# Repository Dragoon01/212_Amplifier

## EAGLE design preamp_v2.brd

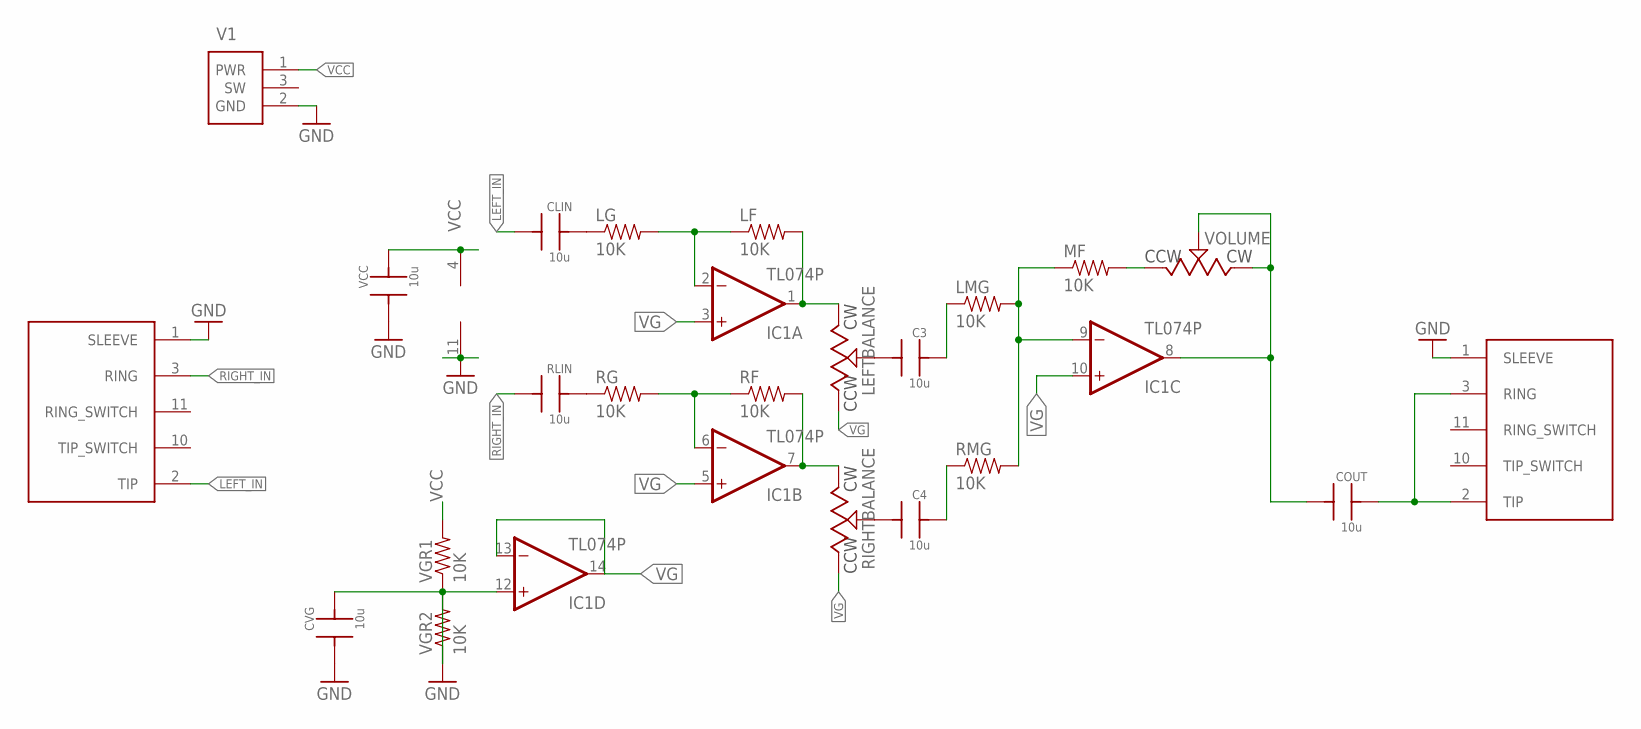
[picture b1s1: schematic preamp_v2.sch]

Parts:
C3, C4: 10u; C322
CLIN: 10u; C322
COUT: 10u; C322
CVG: 10u; C322
IC1: TL074P; DIL14
LEFTBALANCE: POTENTIOMETER3362P; 3362P
LF: 10K; AXIAL-0.4
LG: 10K; AXIAL-0.4
LMG: 10K; AXIAL-0.4
MF: 10K; AXIAL-0.4
RF: 10K; AXIAL-0.4
RG: 10K; AXIAL-0.4
RIGHTBALANCE: POTENTIOMETER3362P; 3362P
RLIN: 10u; C322
RMG: 10K; AXIAL-0.4
U$3, U$4: AUDIO_5_CONDUCTOR; SJ1-3525N
V1: POWER_JACK; PJ-102AH
VCC: 10u; C322
VGR1, VGR2: 10K; AXIAL-0.4
VOLUME: POTENTIOMETER3362P; 3362P

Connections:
GND: CVG.1, IC1.11 (V-), U$3.1 (SLEEVE), U$4.1 (SLEEVE), V1.2 (GND), VCC.1, VGR2.P$2 (2)
LEFT_IN: CLIN.1, U$3.2 (TIP)
unnamed: IC1.2 (-IN), LF.P$1 (1), LG.P$2 (2)
unnamed: IC1.6 (-IN), RF.P$1 (1), RG.P$2 (2)
unnamed: IC1.7 (OUT), RF.P$2 (2), RIGHTBALANCE.3 (CW)
unnamed: IC1.1 (OUT), LEFTBALANCE.3 (CW), LF.P$2 (2)
unnamed: RG.P$1 (1), RLIN.2
unnamed: CLIN.2, LG.P$1 (1)
unnamed: CVG.2, IC1.12 (+IN), VGR1.P$1 (1), VGR2.P$1 (1)
unnamed: C3.1, LEFTBALANCE.2 (WIPER)
unnamed: C3.2, LMG.P$1 (1)
unnamed: C4.2, RMG.P$1 (1)
unnamed: IC1.9 (-IN), LMG.P$2 (2), MF.P$1 (1), RMG.P$2 (2)
unnamed: C4.1, RIGHTBALANCE.2 (WIPER)
unnamed: COUT.1, IC1.8 (OUT), VOLUME.2 (WIPER), VOLUME.3 (CW)
unnamed: COUT.2, U$4.2 (TIP), U$4.3 (RING)
unnamed: MF.P$2 (2), VOLUME.1 (CCW)
RIGHT_IN: RLIN.1, U$3.3 (RING)
SW: V1.3 (SW)
VCC: IC1.4 (V+), V1.1 (PWR), VCC.2, VGR1.P$2 (2)
VG: IC1.3 (+IN), IC1.5 (+IN), IC1.10 (+IN), IC1.13 (-IN), IC1.14 (OUT), LEFTBALANCE.1 (CCW), RIGHTBALANCE.1 (CCW)

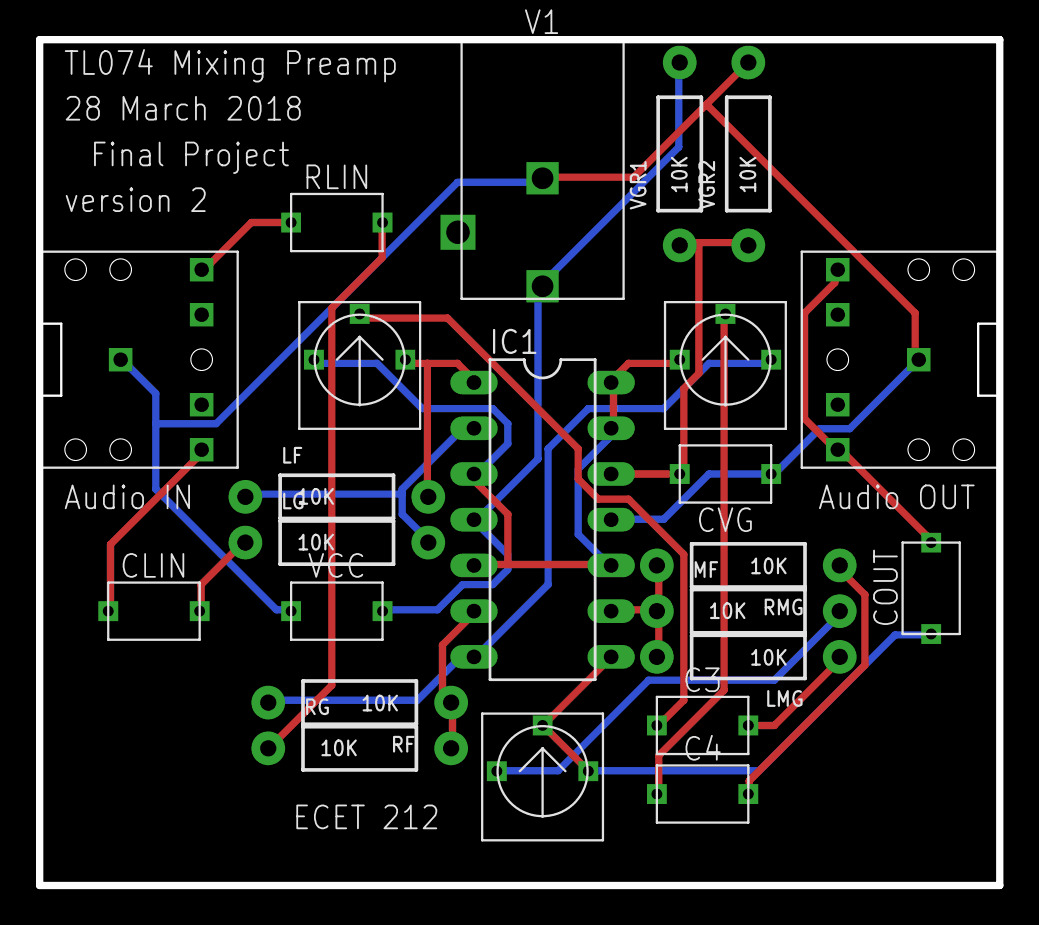
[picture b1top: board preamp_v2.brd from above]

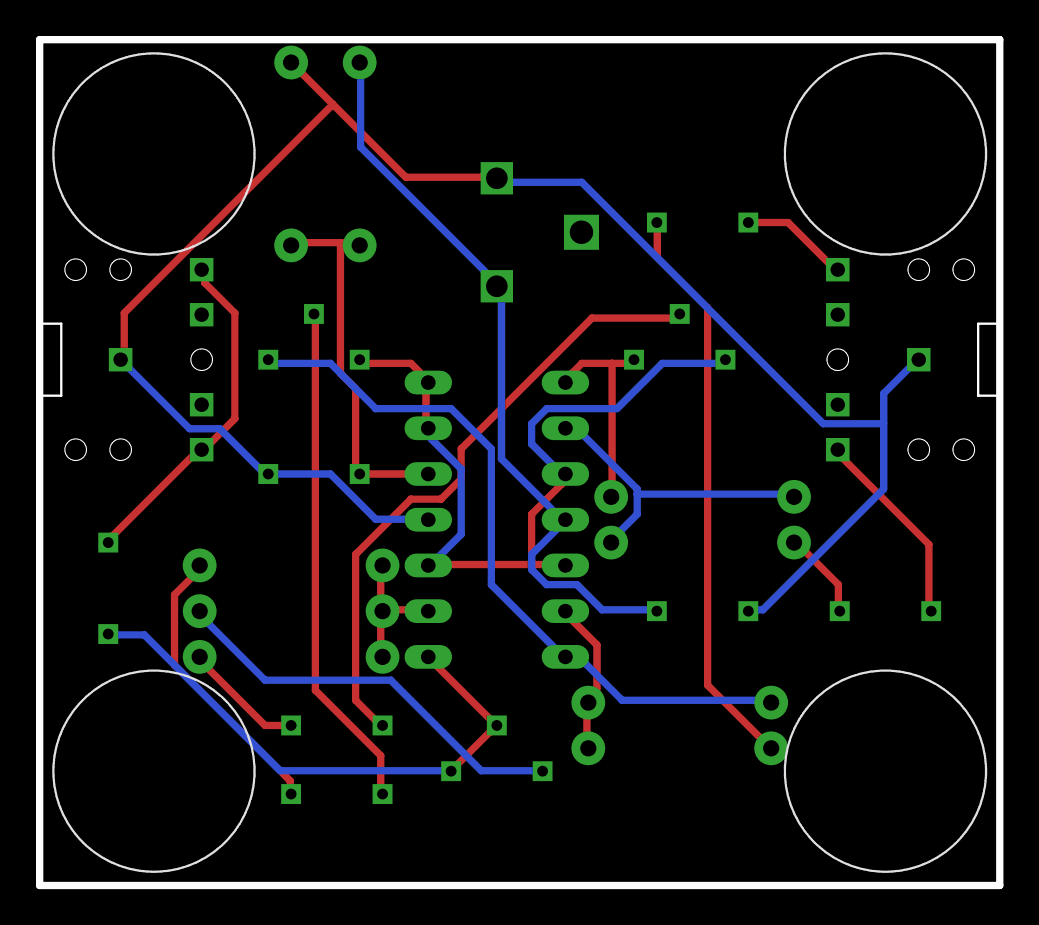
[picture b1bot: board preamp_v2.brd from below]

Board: 2 copper layers, 53.3 x 47.0 mm, 27 parts (4 on the bottom side), 20 nets.

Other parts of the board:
U$7, U$8, U$9, U$10: SJ-5003

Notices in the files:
parts and their libraries:
SparkFun-Passives: Licensing: Creative Commons ShareAlike 4.0 International - https://creativecommons.org/licenses/by-sa/4.0
